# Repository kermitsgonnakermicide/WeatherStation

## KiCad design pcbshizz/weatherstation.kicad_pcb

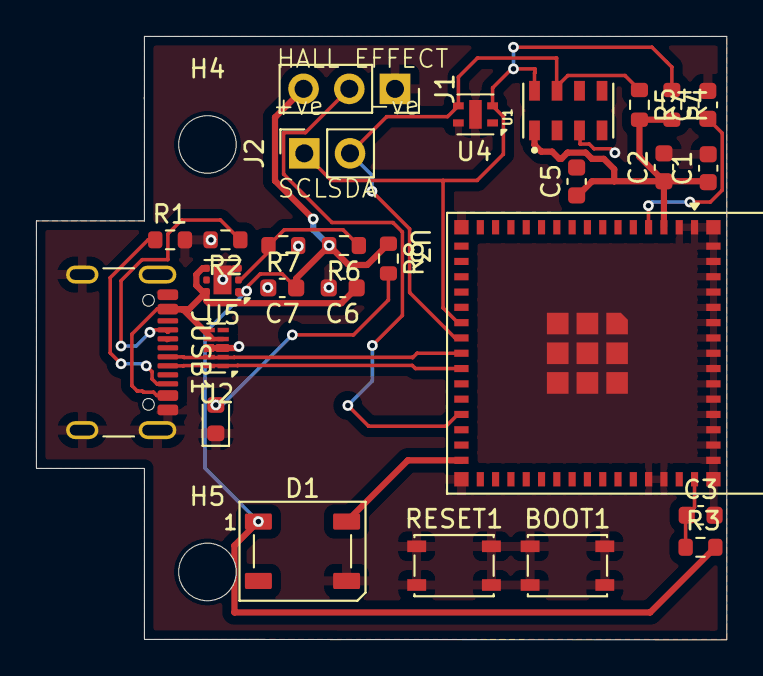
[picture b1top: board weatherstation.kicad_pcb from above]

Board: 4 copper layers, 38.3 x 33.5 mm, 29 parts (0 on the bottom side), 15 nets.

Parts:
BOOT1: SW_SPST_PTS810
C1, C3, C4, C5: 0.1uF; C_0603_1608Metric
C2, C6, C7: 10uF; C_0603_1608Metric
D1: WS2812B; LED_WS2812B_PLCC4_5.0x5.0mm_P3.2mm
D2: LED; LED_0603_1608Metric
H4, H5: MountingHole; MountingHole_3.2mm_M3
J1: Conn_01x03_Socket; PinSocket_1x03_P2.54mm_Vertical
J2: Conn_01x02_Pin; PinSocket_1x02_P2.54mm_Vertical
JUSB1: USB_C_Receptacle_USB2.0; USB_C_Receptacle_GCT_USB4105-xx-A_16P_TopMnt_Horizontal
R1, R2, R8: 5.1k; R_0603_1608Metric
R3, R4, R5: 10k; R_0603_1608Metric
R6: 1M; R_0603_1608Metric
R7: 200k; R_0603_1608Metric
RESET1: SW_SPST_PTS810
U1: MS860702BA01-50; TE_MS860702BA01-50
U2: ESD7104MUTAG; Diodes_UDFN-10_1.0x2.5mm_P0.5mm
U3: ESP32-S3-MINI-1-N8; ESP32-S2-MINI-1
U4: ENS210; AMS_QFN-4-1EP_2x2mm_P0.95mm_EP0.7x1.6mm
U5: TLV75801PDRV; WSON-6-1EP_2x2mm_P0.65mm_EP1x1.6mm

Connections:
/3V3: C1.1, C2.1, C5.1, C7.1, D1.1 (VDD), J1.3, R3.2, R4.2, R5.2, R6.2, R8.1, U1.1 (VDD), U3.3 (3V3), U4.1 (VDD), U5.1 (OUT)
/5VUSB: C6.1, JUSB1.A4 (VBUS), JUSB1.A9 (VBUS), JUSB1.B4 (VBUS), JUSB1.B9 (VBUS), U2.4, U2.7 (NC), U5.4 (EN), U5.6 (IN)
/ESP32_EN: C3.1, R3.1, U3.45 (EN)
/GPIO0: C4.1, U3.4 (IO0)
/GPIO47: J1.2, U3.27 (IO47)
/GPIO48: D1.4 (DIN), U3.30 (IO48)
/I2C_SCL: J2.1, R4.1, U1.8 (SCL), U3.21 (IO17), U4.2 (SCL)
/I2C_SDA: J2.2, R5.1, U1.7 (SDA), U3.22 (IO18), U4.3 (SDA)
/USB_N: JUSB1.A7 (D-), JUSB1.B7 (D-), U2.2, U2.9 (NC), U3.23 (IO19)
/USB_P: JUSB1.A6 (D+), JUSB1.B6 (D+), U2.1, U2.10 (NC), U3.24 (IO20)
GND: BOOT1.1, BOOT1.2, C1.2, C2.2, C3.2, C4.2, C5.2, C6.2, C7.2, D1.3 (VSS), D2.1 (K), J1.1, JUSB1.A1 (GND), JUSB1.A12 (GND), JUSB1.B1 (GND), JUSB1.B12 (GND), JUSB1.S1 (SHIELD), R1.2, R2.2, R7.1, RESET1.1, RESET1.2, U1.3 (GND), U2.3 (VSS), U2.8 (VSS), U3.1 (GND), U3.2 (GND), U3.42 (GND), U3.43 (GND), U3.46 (GND), U3.47 (GND), U3.48 (GND), U3.49 (GND), U3.50 (GND), U3.51 (GND), U3.52 (GND), U3.53 (GND), U3.54 (GND), U3.55 (GND), U3.56 (GND), U3.57 (GND), U3.58 (GND), U3.59 (GND), U3.60 (GND), U3.61 (GND), U3.62 (GND), U3.63 (GND), U3.64 (GND), U3.65 (GND), U4.4 (GND), U4.5 (GND), U5.3 (GND), U5.7 (GND)
unnamed: D2.2 (A), R8.2
unnamed: JUSB1.A5 (CC1), R2.1
unnamed: JUSB1.B5 (CC2), R1.1
unnamed: R6.1, R7.2, U5.2 (FB)

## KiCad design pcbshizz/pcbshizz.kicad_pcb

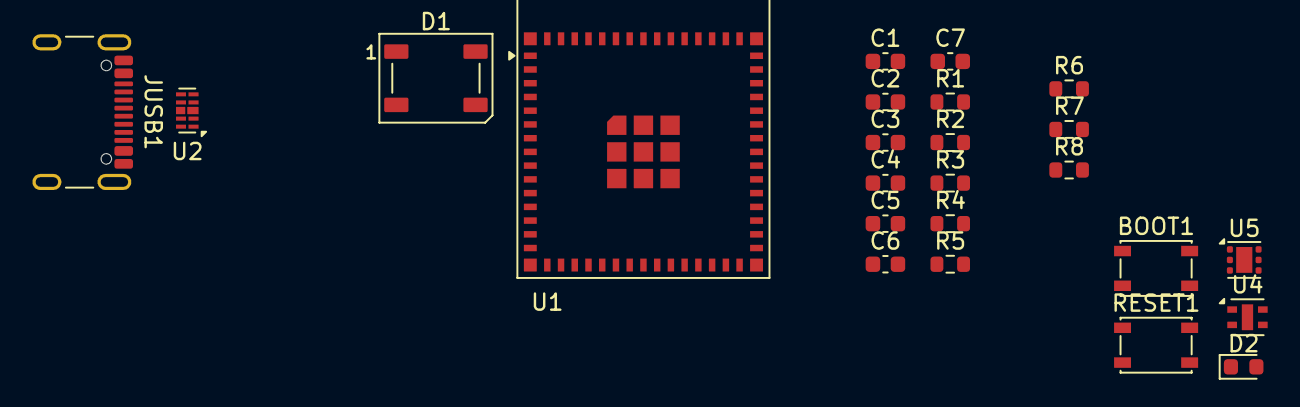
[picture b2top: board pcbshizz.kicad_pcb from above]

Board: 2 copper layers, 24 parts (0 on the bottom side), 15 nets, no tracks yet.

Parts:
BOOT1: SW_SPST_PTS810
C1, C3, C4, C5: 0.1uF; C_0603_1608Metric
C2, C6, C7: 10uF; C_0603_1608Metric
D1: WS2812B; LED_WS2812B_PLCC4_5.0x5.0mm_P3.2mm
D2: LED; LED_0603_1608Metric
JUSB1: USB_C_Receptacle_USB2.0; USB_C_Receptacle_GCT_USB4105-xx-A_16P_TopMnt_Horizontal
R1, R2, R8: 5.1k; R_0603_1608Metric
R3, R4, R5: 10k; R_0603_1608Metric
R6: 1M; R_0603_1608Metric
R7: 200k; R_0603_1608Metric
RESET1: SW_SPST_PTS810
U1: ESP32-S3-MINI-1; ESP32-S2-MINI-1
U2: ESD7104MUTAG; Diodes_UDFN-10_1.0x2.5mm_P0.5mm
U4: ENS210; AMS_QFN-4-1EP_2x2mm_P0.95mm_EP0.7x1.6mm
U5: TLV75801PDRV; WSON-6-1EP_2x2mm_P0.65mm_EP1x1.6mm

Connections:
/3V3: C1.1, C2.1, C5.1, C7.1, D1.1 (VDD), R3.2, R4.2, R5.2, R6.2, R8.1, U4.1 (VDD), U5.1 (OUT)
/5VUSB: C6.1, JUSB1.A4 (VBUS), JUSB1.A9 (VBUS), JUSB1.B4 (VBUS), JUSB1.B9 (VBUS), U2.4, U2.7 (NC), U5.4 (EN), U5.6 (IN)
/ESP32_EN: C3.1, R3.1, U1.45 (EN)
/GPIO0: C4.1, U1.5 (IO1)
/GPIO48: D1.4 (DIN), U1.30 (IO48)
/I2C_SCL: R4.1, U1.22 (IO18), U4.2 (SCL)
/I2C_SDA: R5.1, U4.3 (SDA)
/USB_N: JUSB1.A7 (D-), JUSB1.B7 (D-), U1.23 (USB_D-), U2.2, U2.9 (NC)
/USB_P: JUSB1.A6 (D+), JUSB1.B6 (D+), U1.24 (USB_D+), U2.1, U2.10 (NC)
GND: BOOT1.1, BOOT1.2, C1.2, C2.2, C3.2, C4.2, C5.2, C6.2, C7.2, D1.3 (VSS), D2.1 (K), JUSB1.A1 (GND), JUSB1.A12 (GND), JUSB1.B1 (GND), JUSB1.B12 (GND), JUSB1.S1 (SHIELD), R1.2, R2.2, R7.1, RESET1.1, RESET1.2, U2.3 (VSS), U2.8 (VSS), U4.4 (GND), U4.5 (GND), U5.3 (GND), U5.7 (GND)
unnamed: D2.2 (A), R8.2
unnamed: JUSB1.A5 (CC1), R2.1
unnamed: JUSB1.B5 (CC2), R1.1
unnamed: U1.1 (GND), U1.2 (GND), U1.42 (GND), U1.43 (GND), U1.46 (GND), U1.47 (GND), U1.48 (GND), U1.49 (GND), U1.50 (GND), U1.51 (GND), U1.52 (GND), U1.53 (GND), U1.54 (GND), U1.55 (GND), U1.56 (GND), U1.57 (GND), U1.58 (GND), U1.59 (GND), U1.60 (GND), U1.61 (GND), U1.62 (GND), U1.63 (GND), U1.64 (GND), U1.65 (GND)
unnamed: R6.1, R7.2, U5.2 (FB)

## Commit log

2025-07-15 sigma
2025-07-20 ho gya funny?
2025-07-21 baguette 👍
